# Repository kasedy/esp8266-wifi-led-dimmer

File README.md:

# WiFi controlled LED switch / dimmer

The controller is designed to have extra small size (22x26x14mm), and costs under $2 per item. Four independent channels allow to create lamps with different blink effects or control RGB led strip.
<div style="clear: both;">

Based on ESP8266-01 microcontroller<br/>
Repository store firmware for WiFi controlled LED lamp<br/>
Works with homeassistant<br/>
Supports effects<br/>
Allows to dim light<br/>
Dimming based on PWM<br/>
May work as a WiFi switch<br/>

# Assembling instructions

# Eagle project for pcb manufactering

| Design | Description |
| :---: | --- |
| *Light&#160;SOT32* | Uses SOT32 MOSFET's mounted under voltage regultar. |
| *Light&#160;SOT32&#160;bottom* | Uses SOT32 MOSFET's mounted on the other side of the board. |
| *Light&#160;TO-220* | Uses TO220 MOSFET's for long led strips that requere high power. |
| *Panelized* | Contains all 3 kind of boards replicated 4 times. Archive contains all necessary files for a manufacterer. Board size does not exceed 100X100mm. It is the smalles and cheappes size. Could be ordered from [jlcpcb.com](https://jlcpcb.com/) for $2. |

`Light SOT32` and `Light SOT32 bottom` are low power versions of the board. It can handle up to 2A per chanel. When `Light TO-220` is a high power board with up to 15A per channel.

# Parts required for one module

| Part | Amount |
| --- | :---: |
| Microcontroller Esp8266-01 | 1 |
| MOSFET ao3400 (for low power board version) | 4 |
| MOSFET P55NF06L (for high power board version) | 4 |
| Buck converter Mini 360 | 1 |
| SMD resistor 0805 10kOh | 2 |
| Pin Header 2x4 2.54mm | 1 |
| Terminal KF350-2P and KF350-3P | 2 |
| Terminal KF350-3P | 1 | 
| Male single row pin 2.54mm | 4 |

# Panelized PCB

# Wiring schema

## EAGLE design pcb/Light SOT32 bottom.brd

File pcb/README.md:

# PCB

The controller is designed to have extra small size (22x26x14mm), and costs under $2 per item. Four independent channels allow to create lamps with different blink effects or control RGB led strip.
<div style="clear: both;"><br/><br/><br/></div>

# Assembling instructions

<iframe width="560" height="315" src="https://www.youtube.com/embed/8LverFZVN8w" frameborder="0" allow="accelerometer; autoplay; encrypted-media; gyroscope; picture-in-picture" allowfullscreen></iframe>

# Eagle project for pcb manufactering

| Design | Description |
| :---: | --- |
| *Light&#160;SOT32* | Uses SOT32 MOSFET's mounted under voltage regultar. |
| *Light&#160;SOT32&#160;bottom* | Uses SOT32 MOSFET's mounted on the other side of the board. |
| *Light&#160;TO-220* | Uses TO220 MOSFET's for long led strips that requere high power. |
| *Panelized* | Contains all 3 kind of boards replicated 4 times. Archive contains all necessary files for a manufacterer. Board size does not exceed 100X100mm. It is the smalles and cheappes size. Could be ordered from [jlcpcb.com](https://jlcpcb.com/) for $2. |

`Light SOT32` and `Light SOT32 bottom` are low power versions of the board. It can handle up to 2A per chanel. When `Light TO-220` is a high power board with up to 15A per channel.

# Parts required for one module

| Part | Amount |
| --- | :---: |
| Microcontroller Esp8266-01 | 1 |
| MOSFET ao3400 (for low power board version) | 4 |
| MOSFET P55NF06L (for high power board version) | 4 |
| Buck converter Mini 360 | 1 |
| SMD resistor 0805 10kOh | 2 |
| Pin Header 2x4 2.54mm | 1 |
| Terminal KF350-2P and KF350-3P | 2 |
| Terminal KF350-3P | 1 | 
| Male single row pin 2.54mm | 4 |

# Panelized PCB

# Wiring schema

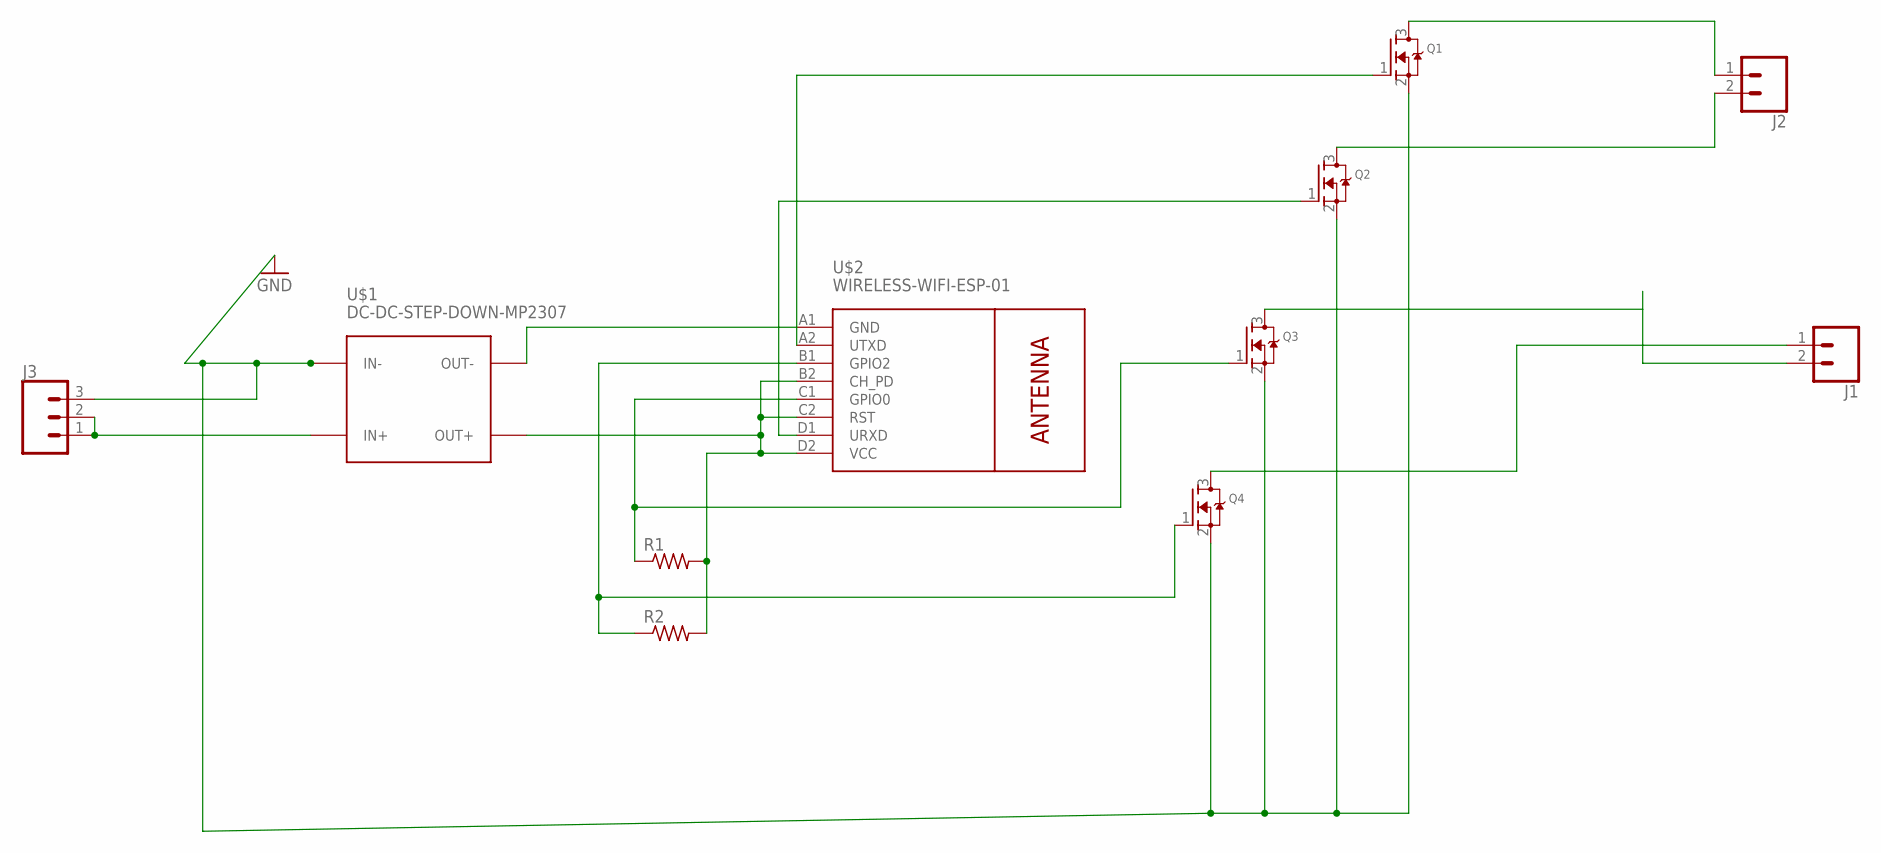
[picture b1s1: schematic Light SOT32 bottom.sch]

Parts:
J1, J2: CONN_023.5MM; SCREWTERMINAL-3.5MM-2
J3: CONN_03SCREW; SCREWTERMINAL-3.5MM-3
Q1, Q2, Q3, Q4: MOSFET-NREFLOW; SOT23
R1, R2: R-US_R0805; R0805
U$1: DC-DC-STEP-DOWN-MP2307
U$2: WIRELESS-WIFI-ESP-01

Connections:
GND: J3.3, Q1.2 (S), Q2.2 (S), Q3.2 (S), Q4.2 (S), U$1.IN-
unnamed: R1.2, R2.2, U$1.OUT+, U$2.B2 (CH_PD), U$2.C2 (RST), U$2.D2 (VCC)
unnamed: Q2.1 (G), U$2.D1 (URXD)
unnamed: U$1.OUT-, U$2.A1 (GND)
unnamed: Q3.1 (G), R1.1, U$2.C1 (GPIO0)
unnamed: Q4.1 (G), R2.1, U$2.B1 (GPIO2)
unnamed: Q1.1 (G), U$2.A2 (UTXD)
unnamed: J3.1, J3.2, U$1.IN+
unnamed: J2.2, Q2.3 (D)
unnamed: J2.1, Q1.3 (D)
unnamed: J1.1, Q4.3 (D)
unnamed: J1.2, Q3.3 (D)

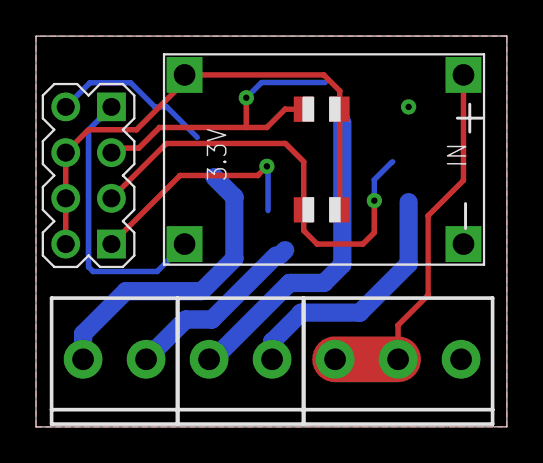
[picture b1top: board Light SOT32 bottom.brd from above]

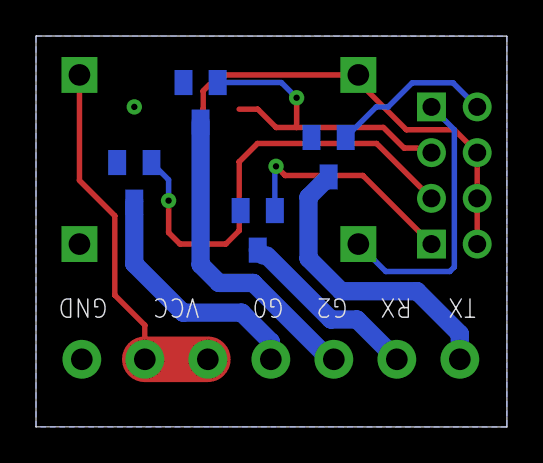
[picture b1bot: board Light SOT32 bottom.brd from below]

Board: 2 copper layers, 26.2 x 21.7 mm, 11 parts (4 on the bottom side), 12 nets.

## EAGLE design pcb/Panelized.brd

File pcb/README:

# Eagle project for manufactering pcb

`Light SOT32` pcb uses SOT32 MOSFET's mounted under voltage regultaro
`Light SOT32 bottom` pcb uses SOT32 MOSFET's mounted on the other side of the board
`Light TO-220` pcb uses TO220 MOSFET's for long led strips that requere more power
`Panelized` contains all 3 kind of boards multiplied 4 times. Archive contains all necessary files for manufacterer. Board size does not exceed 100X100mm. It is the smalles and cheappes size.

# Recomended part list (www.aliexpress.com)

ESP8266: ESP-01
SOT32 MOSFET: ao3400
TO220 MOSFET: P55NF06L
Voltage regulator: Mini 360
Resistors 0805: 10kOh
Pin Header 2x4 Pin 2.54mm 
Terminals: KF350-2P and KF350-3P

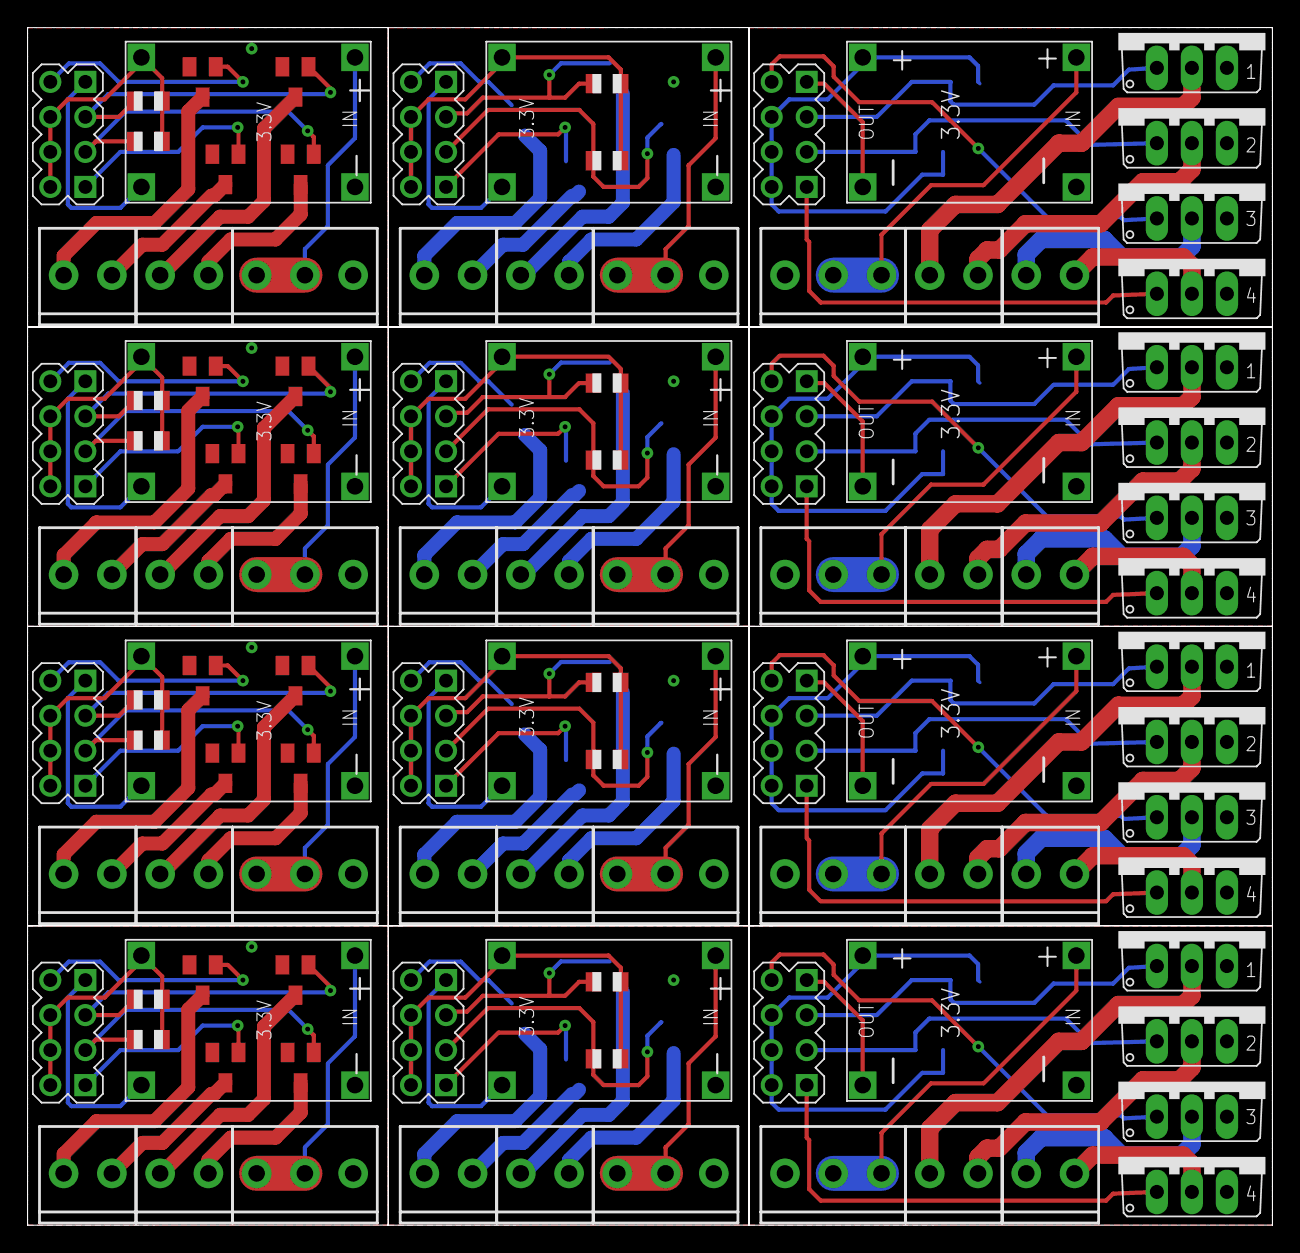
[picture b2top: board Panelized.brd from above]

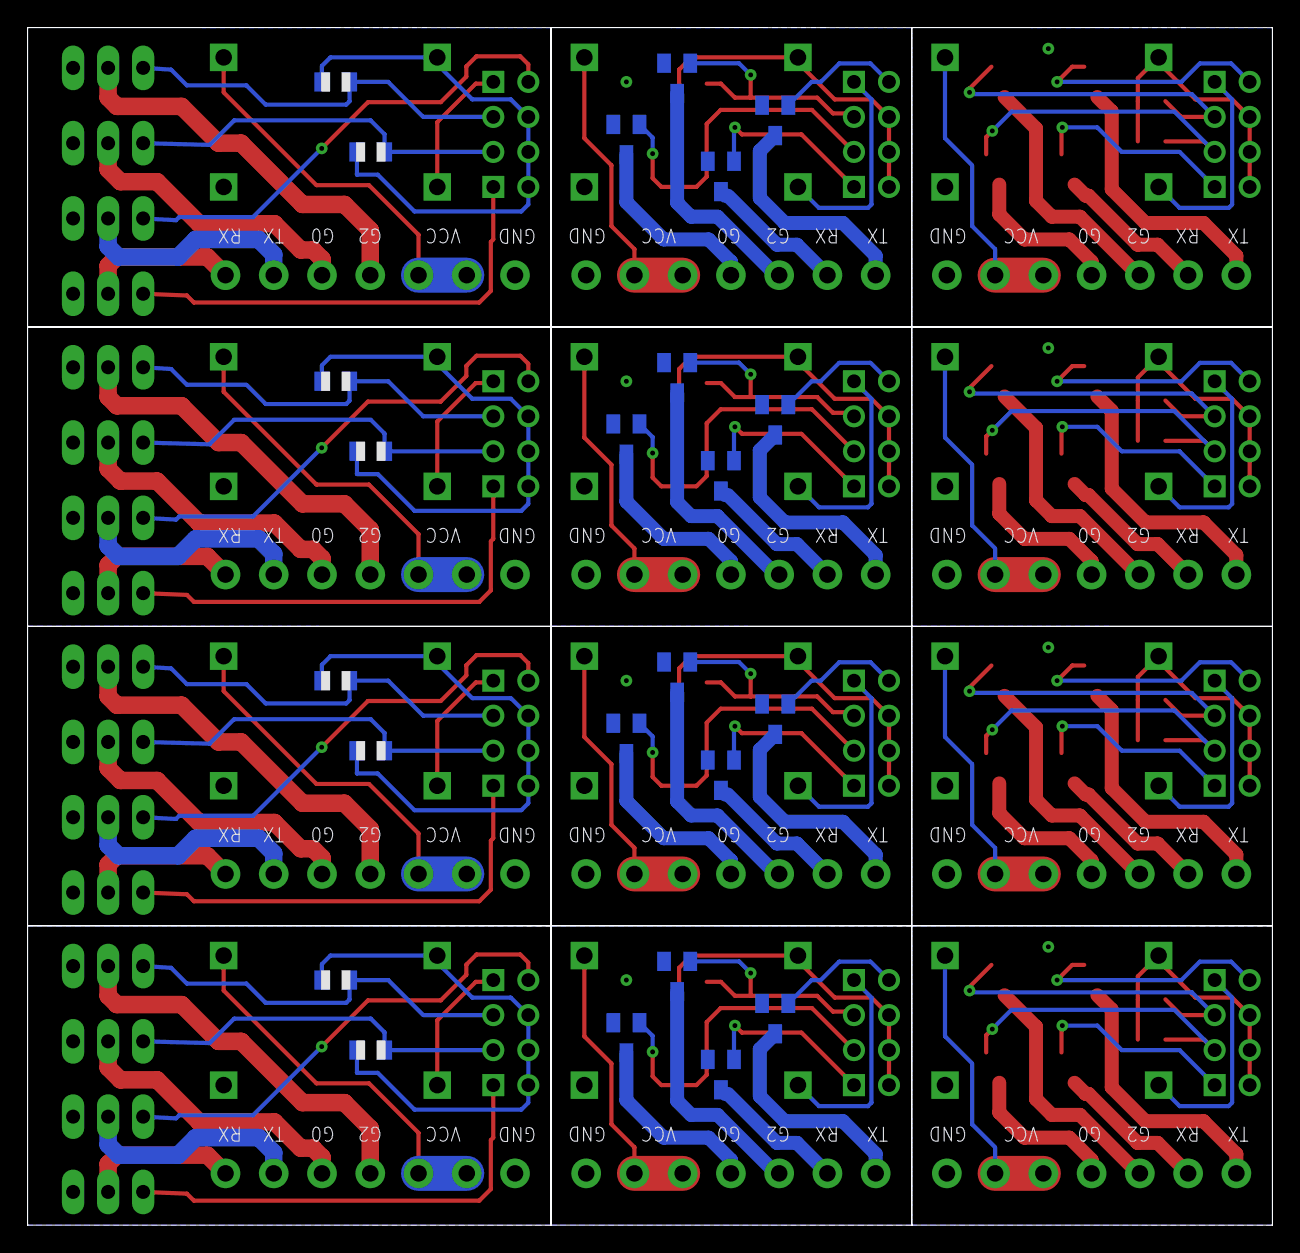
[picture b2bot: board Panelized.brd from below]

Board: 2 copper layers, 90.3 x 86.9 mm, 132 parts (24 on the bottom side), 144 nets.

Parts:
J1, J2, J4, J5, J7, J8, J10, J11, J13, J14, J16, J17, J19, J20, J22, J23, J25, J26, J28, J29, J31, J32, J34, J35: SCREWTERMINAL-3.5MM-2
J3, J6, J9, J12, J15, J18, J21, J24, J27, J30, J33, J36: SCREWTERMINAL-3.5MM-3
Q1, Q2, Q3, Q4, Q5, Q6, Q7, Q8, Q13, Q14, Q15, Q16, Q17, Q18, Q19, Q20, Q25, Q26, Q27, Q28, Q29, Q30, Q31, Q32, Q37, Q38, Q39, Q40, Q41, Q42, Q43, Q44: SOT23
Q9, Q10, Q11, Q12, Q21, Q22, Q23, Q24, Q33, Q34, Q35, Q36, Q45, Q46, Q47, Q48: TO220V
R1, R2, R3, R4, R5, R6, R7, R8, R9, R10, R11, R12, R13, R14, R15, R16, R17, R18, R19, R20, R21, R22, R23, R24: R0805
U$1, U$3, U$5, U$7, U$9, U$11, U$13, U$15, U$17, U$19, U$21, U$23: DC-DC-STEP-DOWN-MP2307
U$2, U$4, U$6, U$8, U$10, U$12, U$14, U$16, U$18, U$20, U$22, U$24: WIRELESS-WIFI-ESP-01

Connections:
GND: J3.3, Q1.2, Q2.2, Q3.2, Q4.2, U$1.IN-
GND1: J6.3, Q5.2, Q6.2, Q7.2, Q8.2, U$3.IN-
GND2: J9.1, Q9.3, Q10.3, Q11.3, Q12.3, U$5.IN-
GND3: J12.3, Q13.2, Q14.2, Q15.2, Q16.2, U$7.IN-
GND4: J15.3, Q17.2, Q18.2, Q19.2, Q20.2, U$9.IN-
GND5: J18.1, Q21.3, Q22.3, Q23.3, Q24.3, U$11.IN-
GND6: J21.3, Q25.2, Q26.2, Q27.2, Q28.2, U$13.IN-
GND7: J24.3, Q29.2, Q30.2, Q31.2, Q32.2, U$15.IN-
GND8: J27.1, Q33.3, Q34.3, Q35.3, Q36.3, U$17.IN-
GND9: J30.3, Q37.2, Q38.2, Q39.2, Q40.2, U$19.IN-
GND10: J33.3, Q41.2, Q42.2, Q43.2, Q44.2, U$21.IN-
GND11: J36.1, Q45.3, Q46.3, Q47.3, Q48.3, U$23.IN-
unnamed: R1.2, R2.2, U$1.OUT+, U$2.B2, U$2.C2, U$2.D2
unnamed: Q2.1, U$2.D1
unnamed: U$1.OUT-, U$2.A1
unnamed: Q3.1, R1.1, U$2.C1
unnamed: Q4.1, R2.1, U$2.B1
unnamed: Q1.1, U$2.A2
unnamed: J3.1, J3.2, U$1.IN+
unnamed: J2.2, Q2.3
unnamed: J2.1, Q1.3
unnamed: J1.1, Q4.3
unnamed: J1.2, Q3.3
unnamed: R3.2, R4.2, U$3.OUT+, U$4.B2, U$4.C2, U$4.D2
unnamed: U$3.OUT-, U$4.A1
unnamed: Q7.1, R3.1, U$4.C1
unnamed: Q8.1, R4.1, U$4.B1
unnamed: Q6.1, U$4.D1
unnamed: Q5.1, U$4.A2
unnamed: J5.2, Q6.3
unnamed: J5.1, Q5.3
unnamed: J4.1, Q8.3
unnamed: J4.2, Q7.3
unnamed: J6.1, J6.2, U$3.IN+
unnamed: R5.2, R6.2, U$5.OUT+, U$6.B2, U$6.C2, U$6.D2
unnamed: U$5.OUT-, U$6.A1
unnamed: Q11.1, R5.1, U$6.C1
unnamed: Q12.1, R6.1, U$6.B1
unnamed: Q10.1, U$6.D1
unnamed: J7.1, Q12.2
unnamed: J7.2, Q11.2
unnamed: J9.2, J9.3, U$5.IN+
unnamed: Q9.1, U$6.A2
unnamed: J8.1, Q9.2
unnamed: J8.2, Q10.2
unnamed: R7.2, R8.2, U$7.OUT+, U$8.B2, U$8.C2, U$8.D2
unnamed: U$7.OUT-, U$8.A1
unnamed: Q15.1, R7.1, U$8.C1
unnamed: Q16.1, R8.1, U$8.B1
unnamed: Q14.1, U$8.D1
unnamed: Q13.1, U$8.A2
unnamed: J11.2, Q14.3
unnamed: J11.1, Q13.3
unnamed: J10.1, Q16.3
unnamed: J10.2, Q15.3
unnamed: J12.1, J12.2, U$7.IN+
unnamed: R9.2, R10.2, U$9.OUT+, U$10.B2, U$10.C2, U$10.D2
unnamed: U$9.OUT-, U$10.A1
unnamed: Q19.1, R9.1, U$10.C1
unnamed: Q20.1, R10.1, U$10.B1
unnamed: Q18.1, U$10.D1
unnamed: Q17.1, U$10.A2
unnamed: J14.2, Q18.3
unnamed: J14.1, Q17.3
unnamed: J13.1, Q20.3
unnamed: J13.2, Q19.3
unnamed: J15.1, J15.2, U$9.IN+
unnamed: R11.2, R12.2, U$11.OUT+, U$12.B2, U$12.C2, U$12.D2
unnamed: U$11.OUT-, U$12.A1
unnamed: Q23.1, R11.1, U$12.C1
unnamed: Q24.1, R12.1, U$12.B1
unnamed: Q22.1, U$12.D1
unnamed: J16.1, Q24.2
unnamed: J16.2, Q23.2
unnamed: J18.2, J18.3, U$11.IN+
unnamed: Q21.1, U$12.A2
unnamed: J17.1, Q21.2
unnamed: J17.2, Q22.2
unnamed: R13.2, R14.2, U$13.OUT+, U$14.B2, U$14.C2, U$14.D2
unnamed: U$13.OUT-, U$14.A1
unnamed: Q27.1, R13.1, U$14.C1
unnamed: Q28.1, R14.1, U$14.B1
unnamed: Q26.1, U$14.D1
unnamed: Q25.1, U$14.A2
unnamed: J20.2, Q26.3
unnamed: J20.1, Q25.3
unnamed: J19.1, Q28.3
unnamed: J19.2, Q27.3
unnamed: J21.1, J21.2, U$13.IN+
unnamed: R15.2, R16.2, U$15.OUT+, U$16.B2, U$16.C2, U$16.D2
unnamed: U$15.OUT-, U$16.A1
unnamed: Q31.1, R15.1, U$16.C1
unnamed: Q32.1, R16.1, U$16.B1
unnamed: Q30.1, U$16.D1
unnamed: Q29.1, U$16.A2
unnamed: J23.2, Q30.3
unnamed: J23.1, Q29.3
unnamed: J22.1, Q32.3
unnamed: J22.2, Q31.3
unnamed: J24.1, J24.2, U$15.IN+
unnamed: R17.2, R18.2, U$17.OUT+, U$18.B2, U$18.C2, U$18.D2
unnamed: U$17.OUT-, U$18.A1
unnamed: Q35.1, R17.1, U$18.C1
unnamed: Q36.1, R18.1, U$18.B1
unnamed: Q34.1, U$18.D1
unnamed: J25.1, Q36.2
unnamed: J25.2, Q35.2
unnamed: J27.2, J27.3, U$17.IN+
unnamed: Q33.1, U$18.A2
unnamed: J26.1, Q33.2
unnamed: J26.2, Q34.2
unnamed: R19.2, R20.2, U$19.OUT+, U$20.B2, U$20.C2, U$20.D2
unnamed: U$19.OUT-, U$20.A1
unnamed: Q39.1, R19.1, U$20.C1
unnamed: Q40.1, R20.1, U$20.B1
unnamed: Q38.1, U$20.D1
unnamed: Q37.1, U$20.A2
unnamed: J29.2, Q38.3
unnamed: J29.1, Q37.3
unnamed: J28.1, Q40.3
unnamed: J28.2, Q39.3
unnamed: J30.1, J30.2, U$19.IN+
unnamed: R21.2, R22.2, U$21.OUT+, U$22.B2, U$22.C2, U$22.D2
unnamed: U$21.OUT-, U$22.A1
unnamed: Q43.1, R21.1, U$22.C1
unnamed: Q44.1, R22.1, U$22.B1
unnamed: Q42.1, U$22.D1
unnamed: Q41.1, U$22.A2
unnamed: J32.2, Q42.3
unnamed: J32.1, Q41.3
unnamed: J31.1, Q44.3
unnamed: J31.2, Q43.3
unnamed: J33.1, J33.2, U$21.IN+
unnamed: R23.2, R24.2, U$23.OUT+, U$24.B2, U$24.C2, U$24.D2
unnamed: U$23.OUT-, U$24.A1
unnamed: Q47.1, R23.1, U$24.C1
unnamed: Q48.1, R24.1, U$24.B1
unnamed: Q46.1, U$24.D1
unnamed: J34.1, Q48.2
unnamed: J34.2, Q47.2
unnamed: J36.2, J36.3, U$23.IN+
unnamed: Q45.1, U$24.A2
unnamed: J35.1, Q45.2
unnamed: J35.2, Q46.2

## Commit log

2019-02-08 added PCB boards
2019-02-08 renaming README -> README.md
2019-02-08 updating readme
2019-02-08 added photos of pcb
2019-02-08 compressed photos
2019-02-08 cleaned unused directories
2019-03-20 do no publish last will, home assistant gets crazy if device connect-disconnect several times
2019-03-20 added home assistant config
2019-05-03 Added simple driver for LEDs that can blink a pattern in cycle.
2019-05-12 Developing a new board with touch sensor
2019-05-12 Added support of touch button
2019-05-13 Added WiFimanager
2019-05-13 Use AsyncMqttClient instead of PubSubClient
2019-05-13 Moved config.h into hardware.h Created Ota module
2019-05-13 Blink with blue led if is in configuration mode
2019-05-14 reset device settings on multiple clicks (>=20)
2019-05-14 updated hardware config
2019-05-15 Improved touch button
2019-08-02 Changed effect number; Fixed linux build; Added remore debug for sensor button;
2019-08-06 Improved Ota module.
2019-08-07 Developing Web portal
2019-08-08 Added emergency protocol (need to be tested)
2019-08-08 Tested STA mode of Emergency protocol
2019-08-09 Changing WiFi manager
2019-08-09 improved emergency protocol and replaced wifi manager
2019-08-09 refactored LightState
2019-08-09 refactoring LightController class
2019-08-09 changed import order
2019-08-10 optimized web portal
2019-08-10 added unit test template, minor fixes
2019-08-12 added secret.ini
2019-08-12 removed secret.ini from commits
2019-08-12 Added void control over IFTTT + adafruit.io
2019-08-13 minor fixes
2019-08-13 cleaned platformio.ini
2019-08-13 removed EmergencyProtocol as unnecessary
2019-08-13 removed CapacitiveSensorButton
2019-08-13 removed debug code
2019-08-13 removed web portal
2019-08-13 removed tests
2019-08-15 fixed brightness regulation over mqtt
